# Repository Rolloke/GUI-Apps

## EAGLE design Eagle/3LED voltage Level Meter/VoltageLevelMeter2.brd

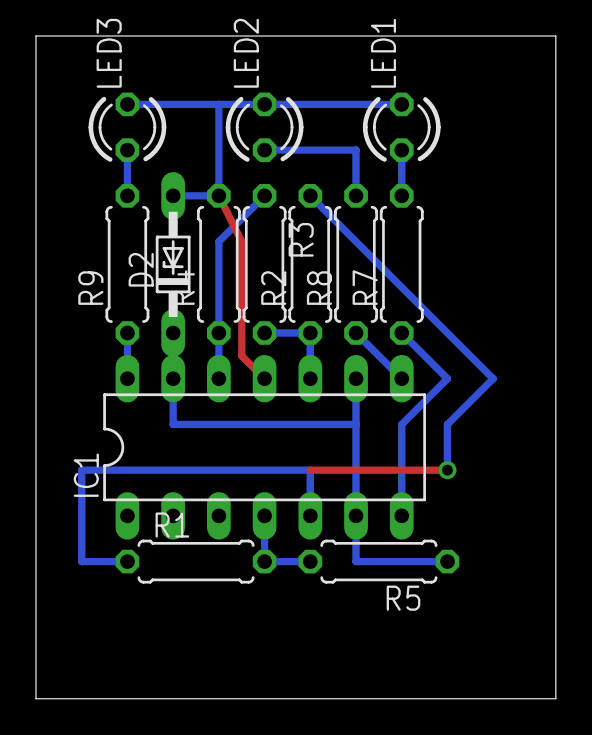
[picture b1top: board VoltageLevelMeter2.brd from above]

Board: 2 copper layers, 28.9 x 36.8 mm, 14 parts (0 on the bottom side), 12 nets.

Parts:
D2: DO34Z7
DRILEGEND: DRILEGEND
IC1: LM324N; DIL14
LED1: red; LED3MM
LED2: Yelllow; LED3MM
LED3: green; LED3MM
R1: 82k; 0207/7
R2: 8k2; 0207/7
R3: 7k5; 0207/7
R4: 33k; 0207/7
R5: 100k; 0207/7
R7, R8, R9: 12k; 0207/7

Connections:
unnamed: IC1.5, R1.1, R2.2
unnamed: IC1.14, R9.1
unnamed: IC1.8, R8.1
unnamed: IC1.7, R7.1
unnamed: IC1.10, R2.1, R3.2
unnamed: IC1.12, R3.1, R4.1
unnamed: LED1.A, R7.2
unnamed: LED2.A, R8.2
unnamed: LED3.A, R9.2
unnamed: D2.C, IC1.6, IC1.9, IC1.13, R5.1
V+: IC1.4, R1.2, R5.2
V-: D2.A, IC1.11, LED1.K, LED2.K, LED3.K, R4.2

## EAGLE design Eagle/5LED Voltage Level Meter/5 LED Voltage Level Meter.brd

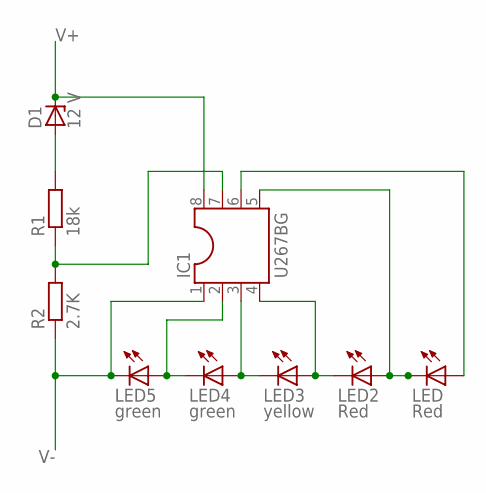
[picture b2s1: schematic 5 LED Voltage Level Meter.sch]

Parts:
D1: 12 V; F126Z10
IC1: U267BG; DIL08
LED, LED2: Red; LED3MM
LED3: yellow; LED3MM
LED4, LED5: green; LED3MM
R1: 18k; 0207/12
R2: 2.7K; 0207/10

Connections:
unnamed: IC1.2, LED4.K (C), LED5.A
unnamed: IC1.3, LED3.K (C), LED4.A
unnamed: IC1.4, LED2.K (C), LED3.A
unnamed: IC1.5, LED.K (C), LED2.A
unnamed: IC1.6, LED.A
unnamed: IC1.7, R1.1, R2.2
unnamed: D1.A, R1.2
V+: D1.C, IC1.8
V-: IC1.1, LED5.K (C), R2.1

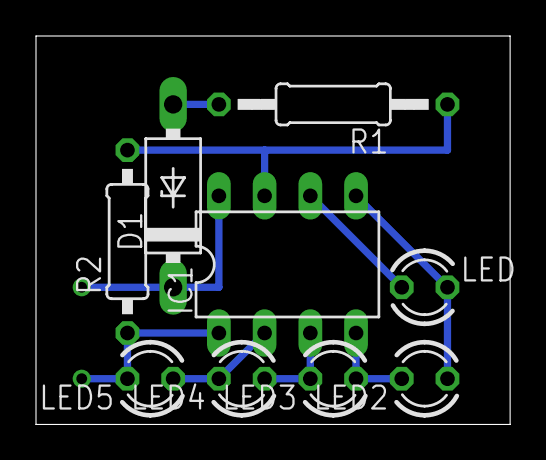
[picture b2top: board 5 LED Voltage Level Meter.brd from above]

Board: 2 copper layers, 26.3 x 21.6 mm, 9 parts (0 on the bottom side), 9 nets.

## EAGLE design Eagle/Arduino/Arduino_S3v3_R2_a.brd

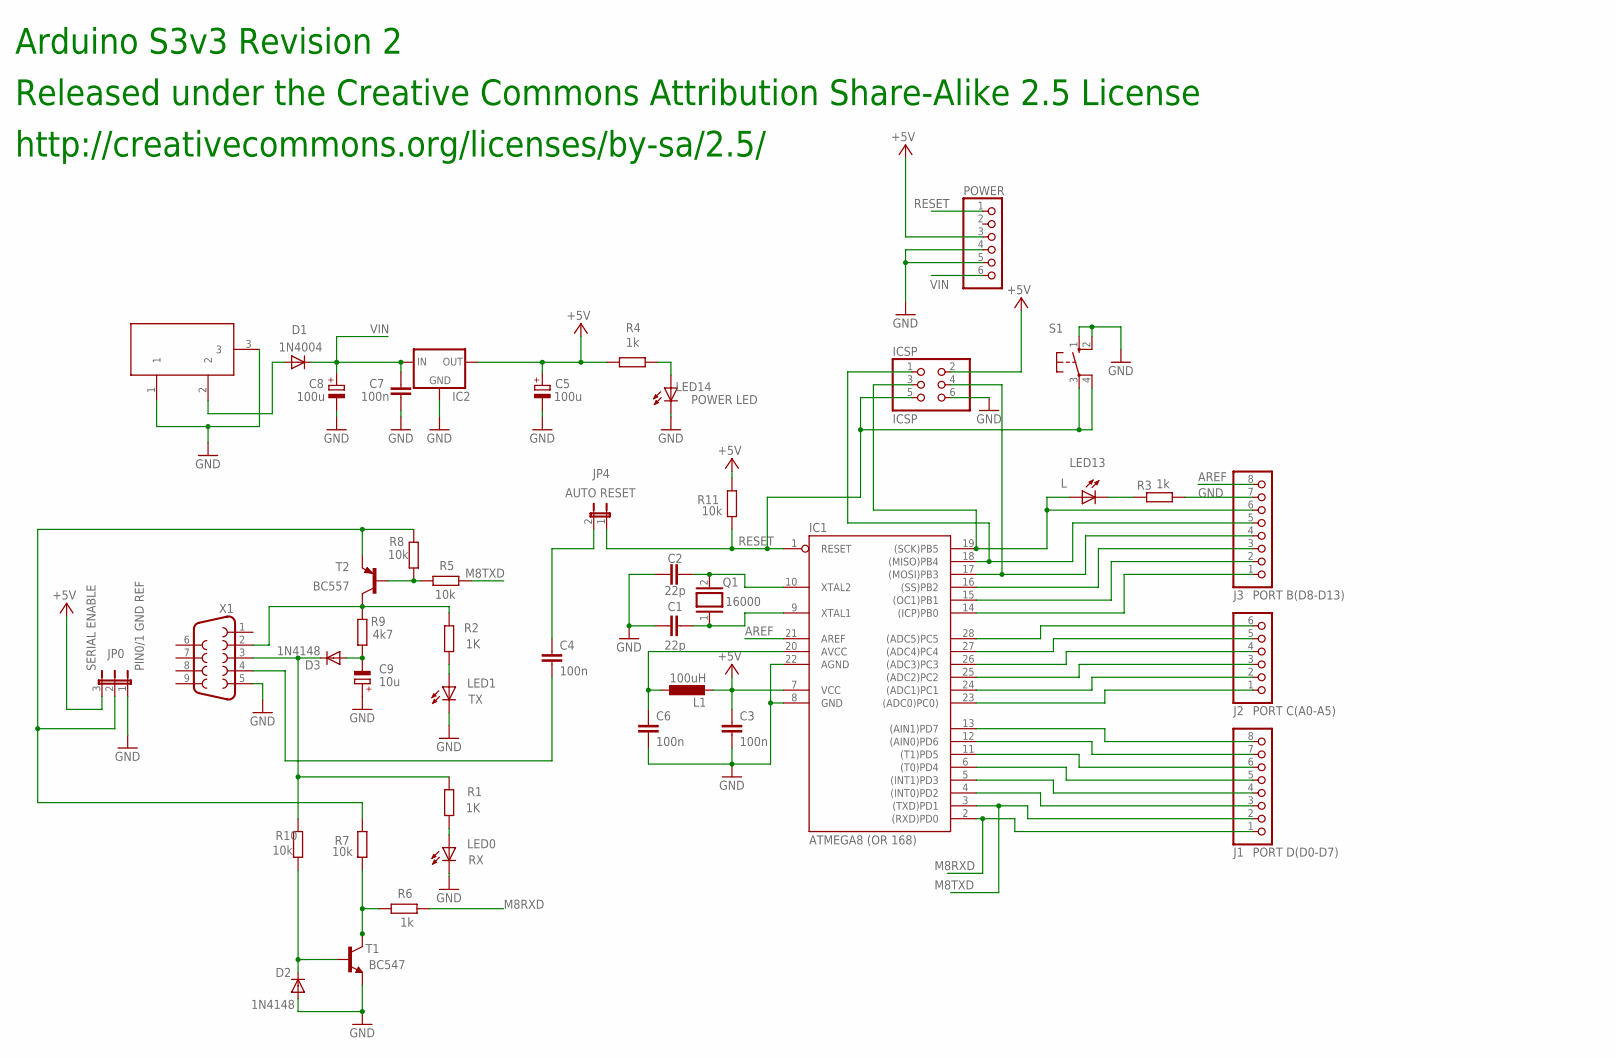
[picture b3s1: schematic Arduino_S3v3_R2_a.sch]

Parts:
C1, C2: 22p; C050-025X075
C3, C4, C6, C7: 100n; C050-025X075
C5, C8: 100u; E3,5-8
C9: 10u; E5-6
D1: 1N4004; DO41-10
D2, D3: 1N4148; DO35-10
DC1: DC21MMX; DC-21MM
IC1: ATMEGA8 (OR 168); DIL28-3
IC2: 78XXL
ICSP: ICSP; 2X03
J1: PORT D(D0-D7); 1X08
J2: PORT C(A0-A5); 1X06
J3: PORT B(D8-D13); 1X08
JP0: JP2W
JP4: AUTO RESET; JP1W
L1: 100uH; 0207/10
LED0: RX; LED3MM
LED1: TX; LED3MM
LED13: L; LED3MM
LED14: POWER LED; LED3MM
POWER: PINHD-1X6; 1X06
Q1: 16000; Q
R1, R2: 1K; 0207/10
R3, R4, R6: 1k; 0207/10
R5, R7, R8, R10, R11: 10k; 0207/10
R9: 4k7; 0207/10
S1: 10-XX; B3F-10XX
T1: BC547; TO92
T2: BC557; TO92-EBC
X1: F09H

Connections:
+5V: C3.1, C5.+, IC1.7 (VCC), IC2.OUT, ICSP.2, JP0.3, L1.2, POWER.3, R4.2, R11.2
AREF: IC1.21 (AREF), J3.8
GND: C1.1, C2.1, C3.2, C5.-, C6.2, C7.1, C8.-, C9.+, D2.A, DC1.1, DC1.3, IC1.8 (GND), IC1.22 (AGND), IC2.GND, ICSP.6, J3.7, JP0.1, LED0.K (C), LED1.K (C), LED14.K (C), POWER.4, POWER.5, R3.1, S1.1 (S), S1.2 (S1), T1.1 (E), X1.5
M8RXD: IC1.2 ((RXD)PD0), J1.1, R6.1
M8TXD: IC1.3 ((TXD)PD1), J1.2, R5.1
unnamed: IC1.18 ((MISO)PB4), ICSP.1, J3.5
unnamed: C9.-, D3.A, R9.1
unnamed: LED14.A, R4.1
unnamed: IC1.17 ((MOSI)PB3), ICSP.4, J3.4
unnamed: IC1.14 ((ICP)PB0), J3.1
unnamed: C1.2, IC1.9 (XTAL1), Q1.1
unnamed: C2.2, IC1.10 (XTAL2), Q1.2
unnamed: D1.A, DC1.2
unnamed: IC1.4 ((INT0)PD2), J1.3
unnamed: IC1.5 ((INT1)PD3), J1.4
unnamed: IC1.6 ((T0)PD4), J1.5
unnamed: IC1.11 ((T1)PD5), J1.6
unnamed: IC1.12 ((AIN0)PD6), J1.7
unnamed: IC1.13 ((AIN1)PD7), J1.8
unnamed: IC1.23 ((ADC0)PC0)), J2.1
unnamed: IC1.24 ((ADC1)PC1), J2.2
unnamed: IC1.25 ((ADC2)PC2), J2.3
unnamed: IC1.26 ((ADC3)PC3), J2.4
unnamed: IC1.27 ((ADC4)PC4), J2.5
unnamed: IC1.28 ((ADC5)PC5), J2.6
unnamed: IC1.15 ((OC1)PB1), J3.2
unnamed: IC1.16 ((SS)PB2), J3.3
unnamed: D3.C, R1.2, R10.2, X1.3
unnamed: R6.2, R7.1, T1.3 (C)
unnamed: R5.2, R8.2, T2.B
unnamed: D2.C, R10.1, T1.2 (B)
unnamed: LED13.K (C), R3.2
unnamed: LED1.A, R2.1
unnamed: LED0.A, R1.1
unnamed: C4.1, JP4.2
unnamed: C4.2, X1.4
unnamed: R2.2, R9.2, T2.C, X1.2
unnamed: C6.1, IC1.20 (AVCC), L1.1
RESET: IC1.1 (RESET), ICSP.5, JP4.1, POWER.1, R11.1, S1.3, S1.4 (P1)
SCK: IC1.19 ((SCK)PB5), ICSP.3, J3.6, LED13.A
SERIAL_VCC: JP0.2, R7.2, R8.1, T2.E
VIN: C7.2, C8.+, D1.C, IC2.IN, POWER.6

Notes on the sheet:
PIN0/1 GND REF
SERIAL ENABLE
Released under the Creative Commons Attribution Share-Alike 2.5 License
http://creativecommons.org/licenses/by-sa/2.5/
Arduino S3v3 Revision 2

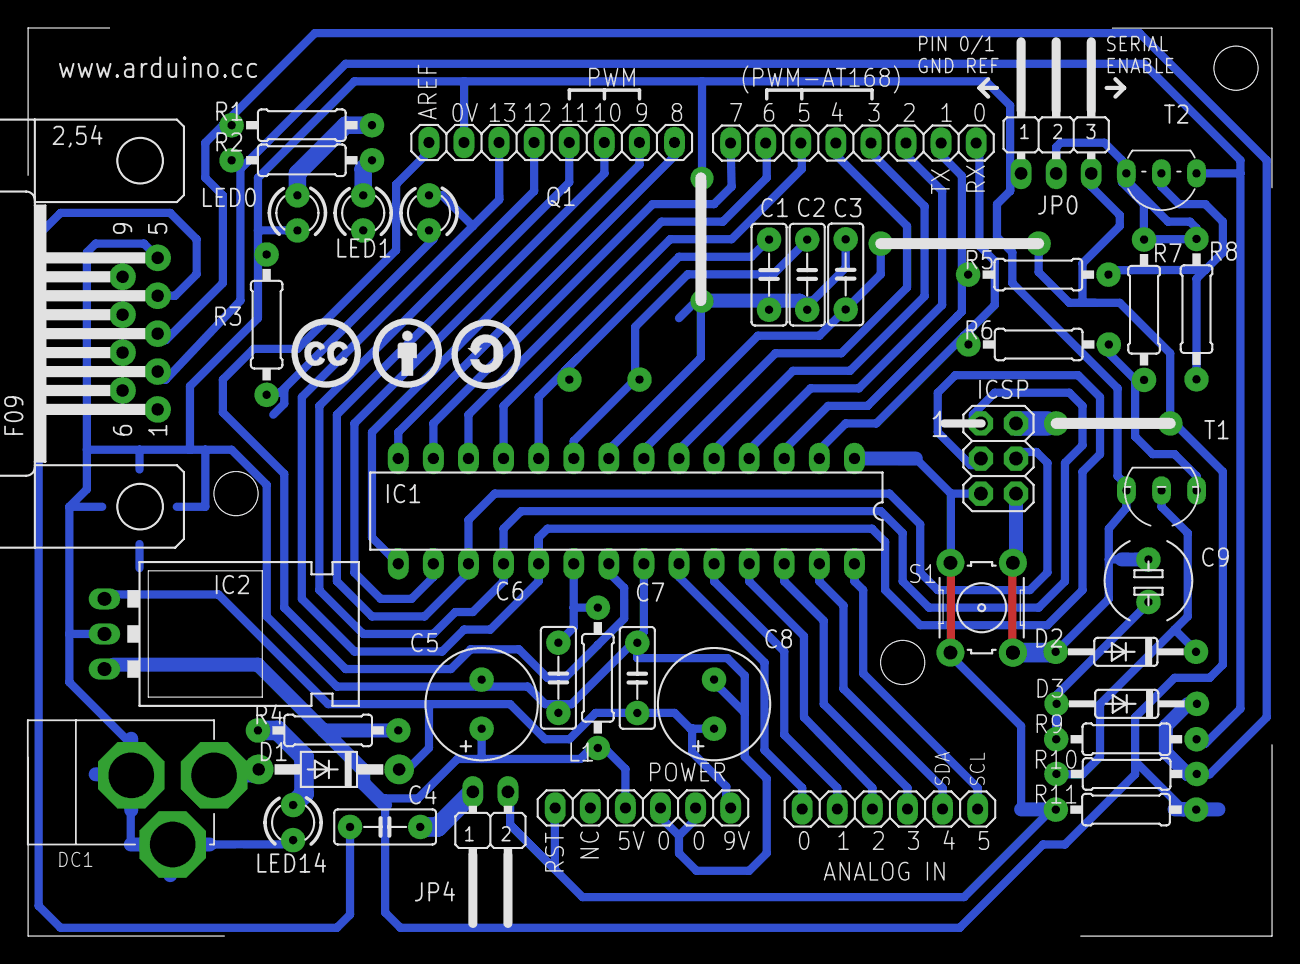
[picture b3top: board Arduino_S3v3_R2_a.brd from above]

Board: 2 copper layers, 90.1 x 65.7 mm, 46 parts (1 on the bottom side), 42 nets.

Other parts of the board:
U$1: CC
U$2: BY
U$3: SA

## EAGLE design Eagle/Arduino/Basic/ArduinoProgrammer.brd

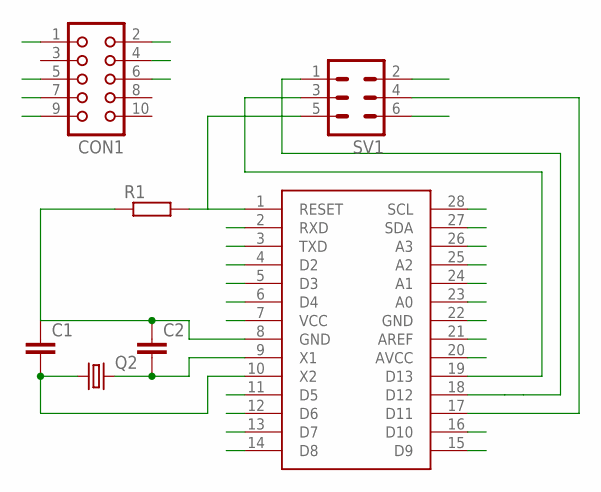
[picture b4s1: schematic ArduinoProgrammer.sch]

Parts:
C1, C2: C-EU025-024X044; C025-024X044
CON1: CON10
Q2: CRYSTALHC49S; HC49/S
R1: R-EU_0207/10; 0207/10
SV1: MA03-2
U$1: ATMEGA328P-PU; DIL28-3

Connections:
A0[MODE]: U$1.23 (A0)
A1: U$1.24 (A1)
A2[MIN]: U$1.25 (A2)
A3[AL]: U$1.26 (A3)
A4[SDA]: U$1.27 (SDA)
A5[SCL]: U$1.28 (SCL)
AREF: U$1.21 (AREF)
DIO1(TX): U$1.3 (TXD)
DIO2[L0]: U$1.4 (D2)
DIO3(PWM)[TONE]: U$1.5 (D3)
DIO4[L1]: U$1.6 (D4)
DIO5(PWM)[AM]: U$1.11 (D5)
DIO6(PWM)[AH]: U$1.12 (D6)
DIO7[L2]: U$1.13 (D7)
DIO8[L3]: U$1.14 (D8)
DIO9(PWM)[SEC]: U$1.15 (D9)
DIO10(PWM)[MIN]: U$1.16 (D10)
DIO11(PWM)MOSI[HR]: CON1.1, SV1.4, U$1.17 (D11)
DIO12/MISO[L4]: CON1.9, SV1.1, U$1.18 (D12)
DPIO0(RX): U$1.2 (RXD)
GND: C1.1, C2.1, CON1.4, R1.1, SV1.6, U$1.8 (GND), U$1.22 (GND)
RESET: R1.2, SV1.5, U$1.1 (RESET)
SCK[L5]: CON1.7, SV1.3, U$1.19 (D13)
VCC: CON1.2, SV1.2, U$1.7 (VCC), U$1.20 (AVCC)
X1: C2.2, Q2.2, U$1.9 (X1)
X2: C1.2, Q2.1, U$1.10 (X2)

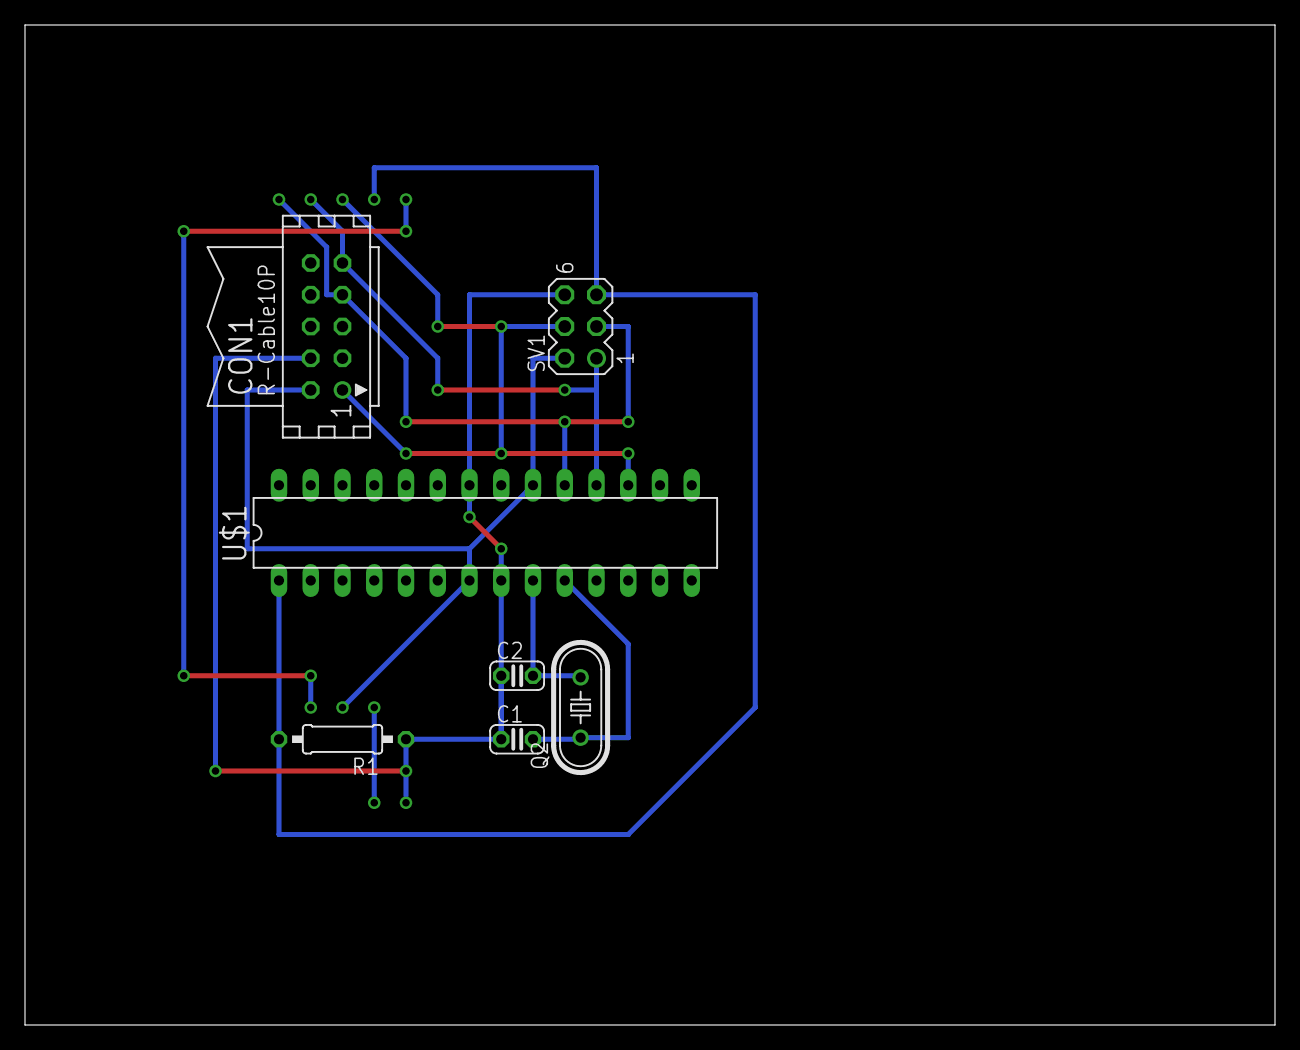
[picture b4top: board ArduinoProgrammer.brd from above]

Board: 2 copper layers, 100.0 x 80.0 mm, 7 parts (0 on the bottom side), 8 nets.

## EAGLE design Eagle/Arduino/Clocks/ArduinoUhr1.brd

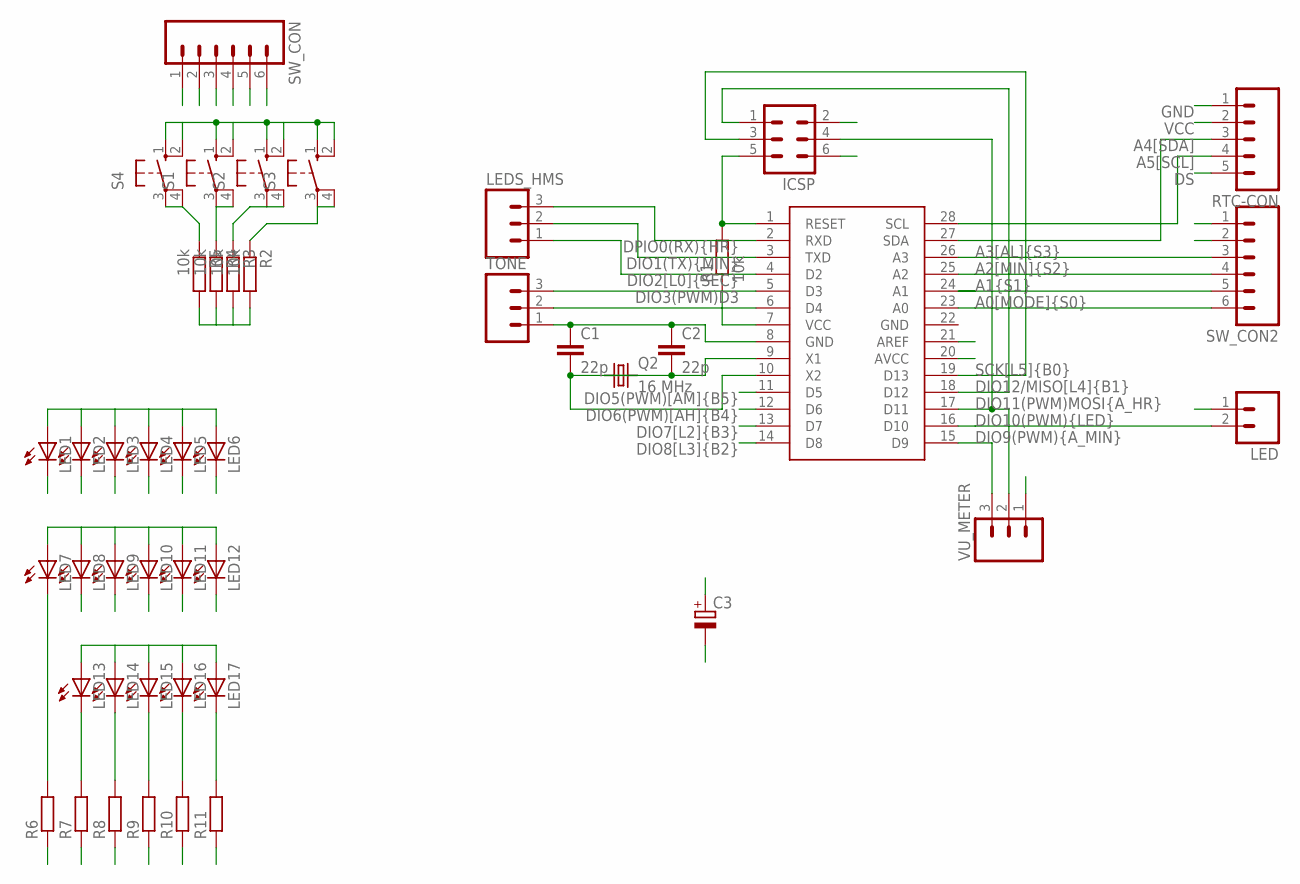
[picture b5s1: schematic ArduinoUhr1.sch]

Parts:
C1, C2: 22p; C025-024X044
C3: CPOL-EUE5-10.5; E5-10,5
ICSP: MA03-2
LED: M02; 02P
LED1, LED2, LED3, LED4, LED5, LED6, LED7, LED8, LED9, LED10, LED11, LED12: LED3MM
LED13, LED14, LED15, LED16, LED17: LED5MM
LEDS_HMS: M03; 03P
Q2: 16 MHz; HC49/S
R1: 10k; 0207/15
R2, R3, R4, R5: 10k; 0204/5
R6, R7, R8, R9, R10, R11: R-EU_0204/7; 0204/7
RTC-CON: M05; 05P
S1, S2, S3, S4: 40-XX; B3F-40XX
SW_CON, SW_CON2: M06; 06P
TONE: M03; 03P
U$1: ATMEGA328P-PU; DIL28-3
VU_METER: M03; 03P

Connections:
A0[MODE]{S0}: SW_CON2.6, U$1.23 (A0)
A1{S1}: SW_CON2.5, U$1.24 (A1)
A2[MIN]{S2}: SW_CON2.4, U$1.25 (A2)
A3[AL]{S3}: SW_CON2.3, U$1.26 (A3)
A4[SDA]: RTC-CON.3, U$1.27 (SDA)
A5[SCL]: RTC-CON.4, U$1.28 (SCL)
AREF: U$1.21 (AREF)
BIT0: R11.1
BIT1: R10.1
BIT2: R9.1
BIT3: R8.1
BIT4: R7.1
BIT5: R6.1
D4: TONE.2, U$1.6 (D4)
DIO1(TX){MIN}: LED7.A, LED8.A, LED9.A, LED10.A, LED11.A, LED12.A, LEDS_HMS.2, U$1.3 (TXD)
DIO2[L0]{SEC}: LED1.A, LED2.A, LED3.A, LED4.A, LED5.A, LED6.A, LEDS_HMS.1, U$1.4 (D2)
DIO3(PWM)D3: TONE.3, U$1.5 (D3)
DIO5(PWM)[AM]{B5}: U$1.11 (D5)
DIO6(PWM)[AH]{B4}: U$1.12 (D6)
DIO7[L2]{B3}: U$1.13 (D7)
DIO8[L3]{B2}: U$1.14 (D8)
DIO9(PWM){A_MIN}: U$1.15 (D9), VU_METER.3
DIO10(PWM){LED}: LED.2, U$1.16 (D10)
DIO11(PWM)MOSI{A_HR}: ICSP.4, U$1.17 (D11), VU_METER.2
DIO12/MISO[L4]{B1}: ICSP.1, U$1.18 (D12)
DPIO0(RX){HR}: LED13.A, LED14.A, LED15.A, LED16.A, LED17.A, LEDS_HMS.3, U$1.2 (RXD)
DS: RTC-CON.5
GND: C1.1, C2.1, C3.-, ICSP.6, LED.1, RTC-CON.1, SW_CON2.2, TONE.1, U$1.8 (GND), VU_METER.1
GND_SW: R2.2, R3.2, R4.2, R5.2, SW_CON.2
LED0: LED6.K (C), LED12.K (C), LED17.K (C), R11.2
LED1: LED5.K (C), LED11.K (C), LED16.K (C), R10.2
LED2: LED4.K (C), LED10.K (C), LED15.K (C), R9.2
LED3: LED3.K (C), LED9.K (C), LED14.K (C), R8.2
LED4: LED2.K (C), LED8.K (C), LED13.K (C), R7.2
LED5: LED1.K (C), LED7.K (C), R6.2
RESET: ICSP.5, R1.2, U$1.1 (RESET)
SCK[L5]{B0}: ICSP.3, U$1.19 (D13)
SW1: R5.1, S4.3, S4.4 (P1), SW_CON.3
SW2: R4.1, S1.3, S1.4 (P1), SW_CON.4
SW3: R3.1, S2.3, S2.4 (P1), SW_CON.5
SW4: R2.1, S3.3, S3.4 (P1), SW_CON.6
VCC: C3.+, ICSP.2, R1.1, RTC-CON.2, SW_CON2.1, U$1.7 (VCC), U$1.20 (AVCC)
VCC_SW: S1.1 (S), S1.2 (S1), S2.1 (S), S2.2 (S1), S3.1 (S), S3.2 (S1), S4.1 (S), S4.2 (S1), SW_CON.1
X1: C2.2, Q2.1, U$1.9 (X1)
X2: C1.2, Q2.2, U$1.10 (X2)

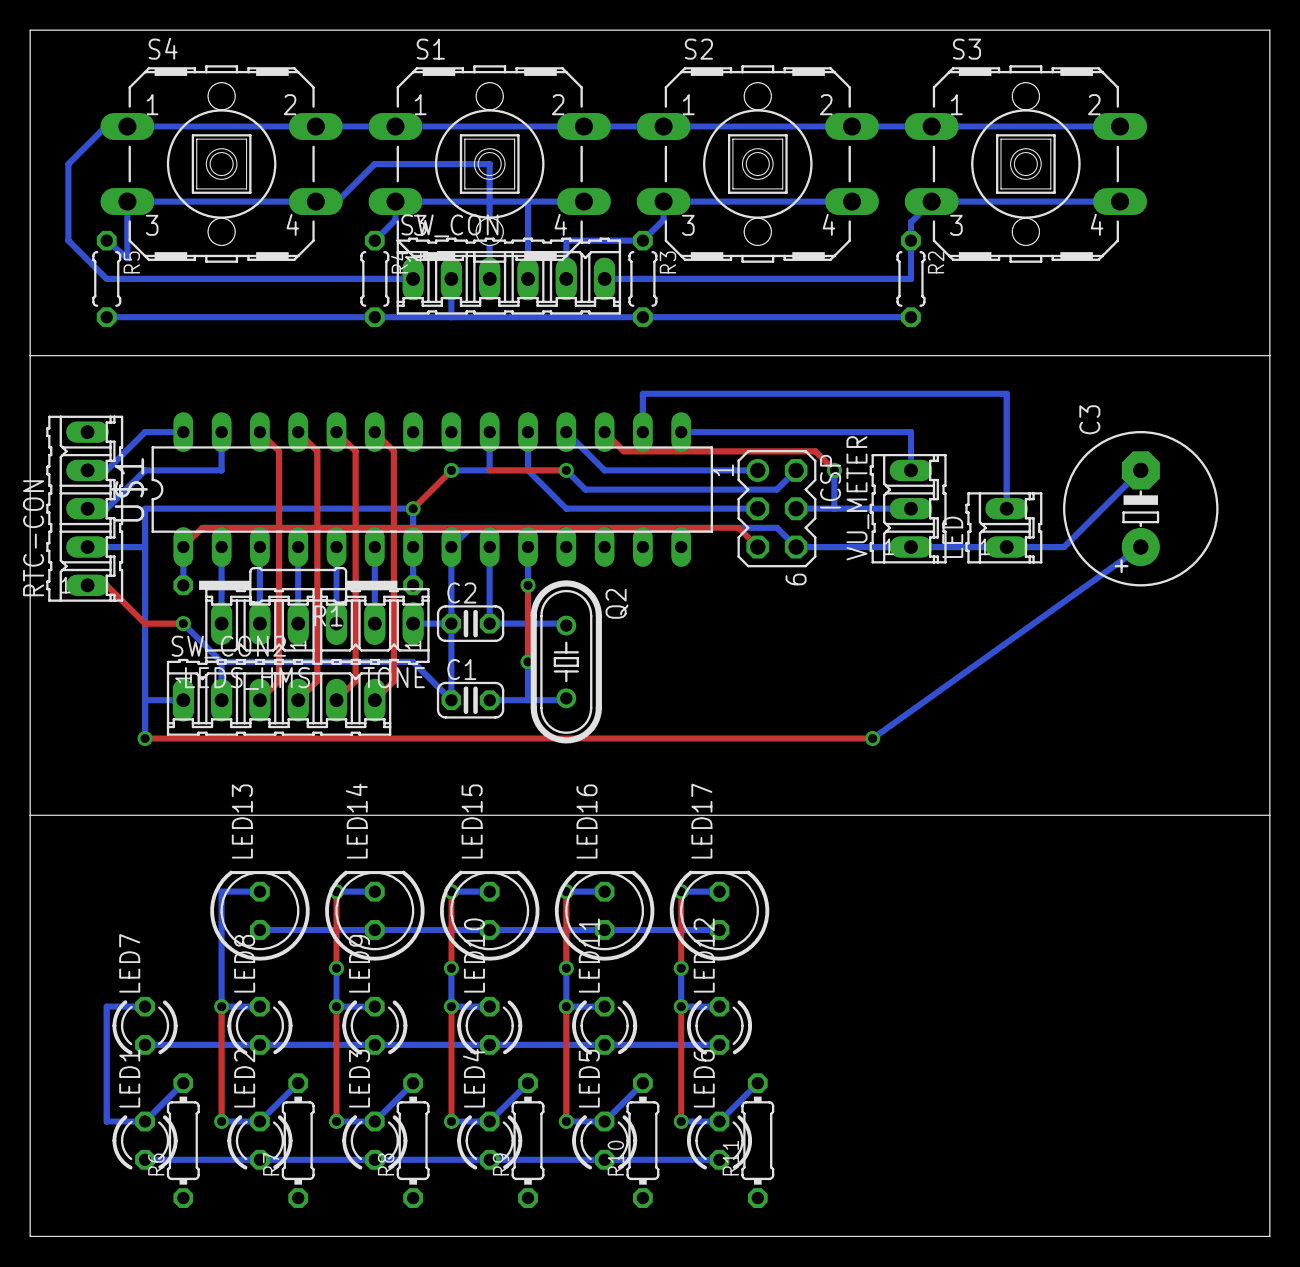
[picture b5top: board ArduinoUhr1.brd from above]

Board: 2 copper layers, 82.2 x 80.0 mm, 45 parts (0 on the bottom side), 33 nets.

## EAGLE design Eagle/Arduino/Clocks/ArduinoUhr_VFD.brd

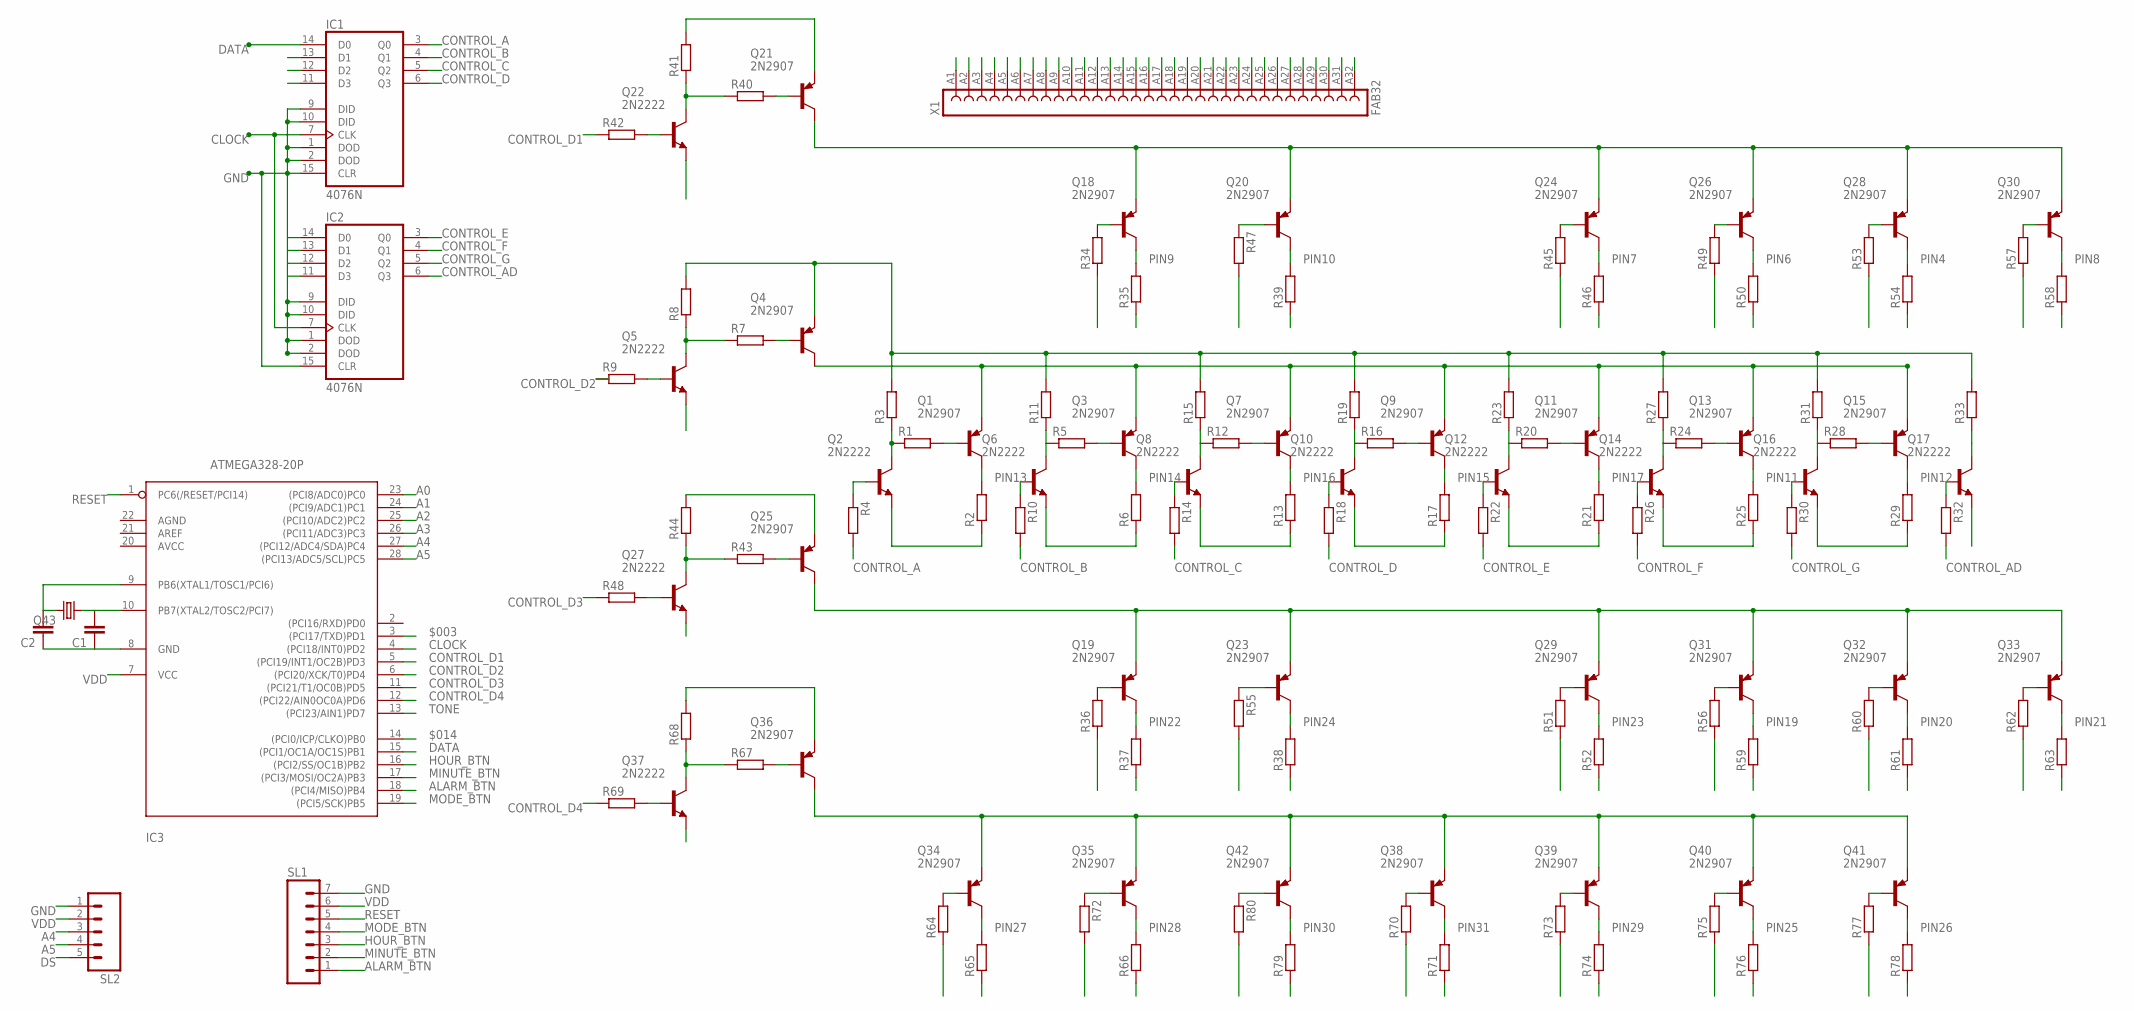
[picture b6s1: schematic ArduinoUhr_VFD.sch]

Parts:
C1, C2: C-EU025-024X044; C025-024X044
IC1, IC2: 4076N; DIL16
IC3: ATMEGA328-20P; DIL28-3
Q1, Q3, Q4, Q7, Q9, Q11, Q13, Q15, Q18, Q19, Q20, Q21, Q23, Q24, Q25, Q26, Q28, Q29, Q30, Q31, Q32, Q33, Q34, Q35, Q36, Q38, Q39, Q40, Q41, Q42: 2N2907; TO18
Q2, Q5, Q6, Q8, Q10, Q12, Q14, Q16, Q17, Q22, Q27, Q37: 2N2222; TO18
Q43: CRYSTALHC49S; HC49/S
R1, R12, R20, R28, R34, R53, R55, R57, R60, R62, R72, R73, R75: R-EU_0411/3V; 0411V
R2, R3, R4, R5, R6, R9, R10, R11, R13, R14, R15, R16, R17, R18, R19, R21, R22, R23, R24, R25, R26, R27, R29, R30, R31, R32, R33, R35, R36, R37, R38, R39, R42, R45, R46, R47, R48, R49, R50, R51, R52, R54, R56, R58, R59, R61, R63, R64, R65, R66, R69, R70, R71, R74, R76, R77, R78, R79, R80: R-EU_0204/7; 0204/7
R7, R8, R40, R41, R43, R44, R67, R68: R-EU_0204/2V; 0204V
SL1: M07; 07P
SL2: M05; 05P
X1: FAB32

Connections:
$003: IC3.3 ((PCI17/TXD)PD1)
$014: IC3.14 ((PCI0/ICP/CLKO)PB0)
A0: IC3.23 ((PCI8/ADC0)PC0)
A1: IC3.24 ((PCI9/ADC1)PC1)
A2: IC3.25 ((PCI10/ADC2)PC2)
A3: IC3.26 ((PCI11/ADC3)PC3)
A4: IC3.27 ((PCI12/ADC4/SDA)PC4), SL2.3
A5: IC3.28 ((PCI13/ADC5/SCL)PC5), SL2.4
ALARM_BTN: IC3.18 ((PCI4/MISO)PB4), SL1.1
CI_A: Q2.3 (C), R1.1, R3.1, R64.1
CI_AD: Q17.3 (C), R33.1, R57.1, R62.1
CI_B: Q6.3 (C), R5.1, R11.1, R34.1, R36.1, R72.2
CI_C: Q8.3 (C), R12.1, R15.1, R47.2, R55.2, R80.2
CI_D: Q10.3 (C), R16.1, R19.1, R70.1
CI_E: Q12.3 (C), R20.1, R23.1, R45.1, R51.1, R73.1
CI_F: Q14.3 (C), R24.1, R27.1, R49.1, R56.1, R75.1
CI_G: Q16.3 (C), R28.1, R31.1, R53.1, R60.1, R77.1
CLOCK: IC1.7 (CLK), IC2.7 (CLK), IC3.4 ((PCI18/INT0)PD2)
CONTROL_A: IC1.3 (Q0), IC1.13 (D1), R4.2
CONTROL_AD: IC2.6 (Q3), R32.2
CONTROL_B: IC1.4 (Q1), IC1.12 (D2), R10.2
CONTROL_C: IC1.5 (Q2), IC1.11 (D3), R14.2
CONTROL_D: IC1.6 (Q3), IC2.14 (D0), R18.2
CONTROL_D1: IC3.5 ((PCI19/INT1/OC2B)PD3), R42.1
CONTROL_D2: IC3.6 ((PCI20/XCK/T0)PD4), R9.1
CONTROL_D3: IC3.11 ((PCI21/T1/OC0B)PD5), R48.1
CONTROL_D4: IC3.12 ((PCI22/AIN0OC0A)PD6), R69.1
CONTROL_E: IC2.3 (Q0), IC2.13 (D1), R22.2
CONTROL_F: IC2.4 (Q1), IC2.12 (D2), R26.2
CONTROL_G: IC2.5 (Q2), IC2.11 (D3), R30.2
DATA: IC1.14 (D0), IC3.15 ((PCI1/OC1A/OC1S)PB1)
DS: SL2.5
GND: C1.1, C2.1, IC1.1 (DOD), IC1.2 (DOD), IC1.9 (DID), IC1.10 (DID), IC1.15 (CLR), IC2.1 (DOD), IC2.2 (DOD), IC2.9 (DID), IC2.10 (DID), IC2.15 (CLR), IC3.8 (GND), Q2.1 (E), Q5.1 (E), Q6.1 (E), Q8.1 (E), Q10.1 (E), Q12.1 (E), Q14.1 (E), Q16.1 (E), Q17.1 (E), Q22.1 (E), Q27.1 (E), Q37.1 (E), R2.1, R6.1, R13.1, R17.1, R21.1, R25.1, R29.1, R35.1, R37.1, R38.1, R39.1, R46.1, R50.1, R52.1, R54.1, R58.1, R59.1, R61.1, R63.1, R65.1, R66.1, R71.1, R74.1, R76.1, R78.1, R79.1, SL1.7, SL2.1
HOUR_BTN: IC3.16 ((PCI2/SS/OC1B)PB2), SL1.3
MINUTE_BTN: IC3.17 ((PCI3/MOSI/OC2A)PB3), SL1.2
MODE_BTN: IC3.19 ((PCI5/SCK)PB5), SL1.4
unnamed: Q5.2 (B), R9.2
unnamed: Q35.2 (B), R72.1
unnamed: Q1.2 (B), R1.2
unnamed: Q42.2 (B), R80.1
unnamed: Q3.2 (B), R5.2
unnamed: Q2.2 (B), R4.1
unnamed: Q4.2 (B), R7.2
unnamed: Q5.3 (C), R7.1, R8.1
unnamed: Q18.2 (B), R34.2
unnamed: Q6.2 (B), R10.1
unnamed: Q23.2 (B), R55.1
unnamed: Q20.2 (B), R47.1
unnamed: Q15.2 (B), R28.2
unnamed: Q7.2 (B), R12.2
unnamed: Q21.2 (B), R40.2
unnamed: Q8.2 (B), R14.1
unnamed: Q17.2 (B), R32.1
unnamed: C1.2, IC3.10 (PB7(XTAL2/TOSC2/PCI7)), Q43.1
unnamed: Q22.3 (C), R40.1, R41.1
unnamed: Q9.2 (B), R16.2
unnamed: Q22.2 (B), R42.2
unnamed: Q10.2 (B), R18.1
unnamed: C2.2, IC3.9 (PB6(XTAL1/TOSC1/PCI6)), Q43.2
unnamed: Q16.2 (B), R30.1
unnamed: Q11.2 (B), R20.2
unnamed: Q12.2 (B), R22.1
unnamed: Q24.2 (B), R45.2
unnamed: Q13.2 (B), R24.2
unnamed: Q14.2 (B), R26.1
unnamed: Q26.2 (B), R49.2
unnamed: Q19.2 (B), R36.2
unnamed: Q28.2 (B), R53.2
unnamed: Q25.2 (B), R43.2
unnamed: Q30.2 (B), R57.2
unnamed: Q27.3 (C), R43.1, R44.1
unnamed: Q27.2 (B), R48.2
unnamed: Q29.2 (B), R51.2
unnamed: Q31.2 (B), R56.2
unnamed: Q32.2 (B), R60.2
unnamed: Q33.2 (B), R62.2
unnamed: Q34.2 (B), R64.2
unnamed: Q36.2 (B), R67.2
unnamed: Q37.3 (C), R67.1, R68.1
unnamed: Q37.2 (B), R69.2
unnamed: Q38.2 (B), R70.2
unnamed: Q39.2 (B), R73.2
unnamed: Q40.2 (B), R75.2
unnamed: Q41.2 (B), R77.2
PIN1: X1.A1 (1)
PIN2: X1.A2 (2)
PIN3: X1.A3 (3)
PIN4: Q28.3 (C), R54.2, X1.A4 (4)
PIN5: X1.A5 (5)
PIN6: Q26.3 (C), R50.2, X1.A6 (6)
PIN7: Q24.3 (C), R46.2, X1.A7 (7)
PIN8: Q30.3 (C), R58.2, X1.A8 (8)
PIN9: Q18.3 (C), R35.2, X1.A9 (9)
PIN10: Q20.3 (C), R39.2, X1.A10 (10)
PIN11: Q13.3 (C), R25.2, X1.A11 (11)
PIN12: Q15.3 (C), R29.2, X1.A12 (12)
PIN13: Q1.3 (C), R2.2, X1.A13 (13)
PIN14: Q3.3 (C), R6.2, X1.A14 (14)
PIN15: Q9.3 (C), R17.2, X1.A15 (15)
PIN16: Q7.3 (C), R13.2, X1.A16 (16)
PIN17: Q11.3 (C), R21.2, X1.A17 (17)
PIN18: X1.A18 (18)
PIN19: Q31.3 (C), R59.2, X1.A19 (19)
PIN20: Q32.3 (C), R61.2, X1.A20 (20)
PIN21: Q33.3 (C), R63.2, X1.A21 (21)
PIN22: Q19.3 (C), R37.2, X1.A22 (22)
PIN23: Q29.3 (C), R52.2, X1.A23 (23)
PIN24: Q23.3 (C), R38.2, X1.A24 (24)
PIN25: Q40.3 (C), R76.2, X1.A25 (25)
PIN26: Q41.3 (C), R78.2, X1.A26 (26)
PIN27: Q34.3 (C), R65.2, X1.A27 (27)
PIN28: Q35.3 (C), R66.2, X1.A28 (28)
PIN29: Q39.3 (C), R74.2, X1.A29 (29)
PIN30: Q42.3 (C), R79.2, X1.A30 (30)
PIN31: Q38.3 (C), R71.2, X1.A31 (31)
PIN32: X1.A32 (32)
RESET: IC3.1 (PC6(/RESET/PCI14)), SL1.5
TONE: IC3.13 ((PCI23/AIN1)PD7)
VDD: IC1.16 (VDD), IC2.16 (VDD), IC3.7 (VCC), SL1.6, SL2.2
VSS: IC1.8 (VSS), IC2.8 (VSS)
V_D1: Q18.1 (E), Q20.1 (E), Q21.3 (C), Q24.1 (E), Q26.1 (E), Q28.1 (E), Q30.1 (E)
V_D2: Q1.1 (E), Q3.1 (E), Q4.3 (C), Q7.1 (E), Q9.1 (E), Q11.1 (E), Q13.1 (E), Q15.1 (E)
V_D3: Q19.1 (E), Q23.1 (E), Q25.3 (C), Q29.1 (E), Q31.1 (E), Q32.1 (E), Q33.1 (E)
V_D4: Q34.1 (E), Q35.1 (E), Q36.3 (C), Q38.1 (E), Q39.1 (E), Q40.1 (E), Q41.1 (E), Q42.1 (E)
V_VFD: Q4.1 (E), Q21.1 (E), Q25.1 (E), Q36.1 (E), R3.2, R8.2, R11.2, R15.2, R19.2, R23.2, R27.2, R31.2, R33.2, R41.2, R44.2, R68.2

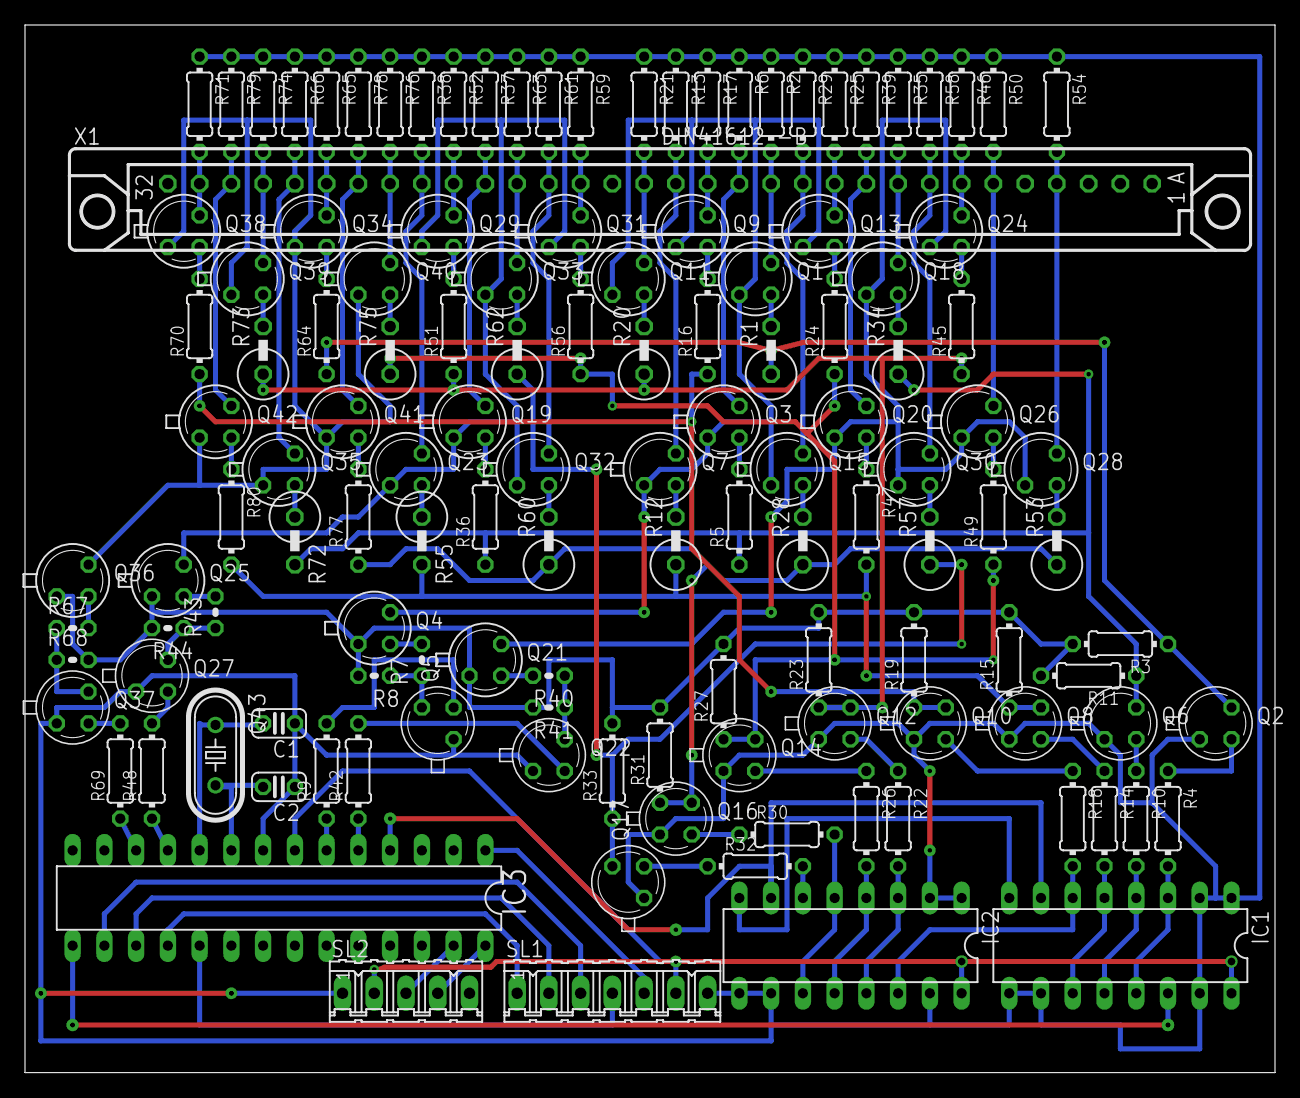
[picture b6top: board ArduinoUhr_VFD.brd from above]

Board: 2 copper layers, 100.0 x 83.8 mm, 131 parts (0 on the bottom side), 111 nets.

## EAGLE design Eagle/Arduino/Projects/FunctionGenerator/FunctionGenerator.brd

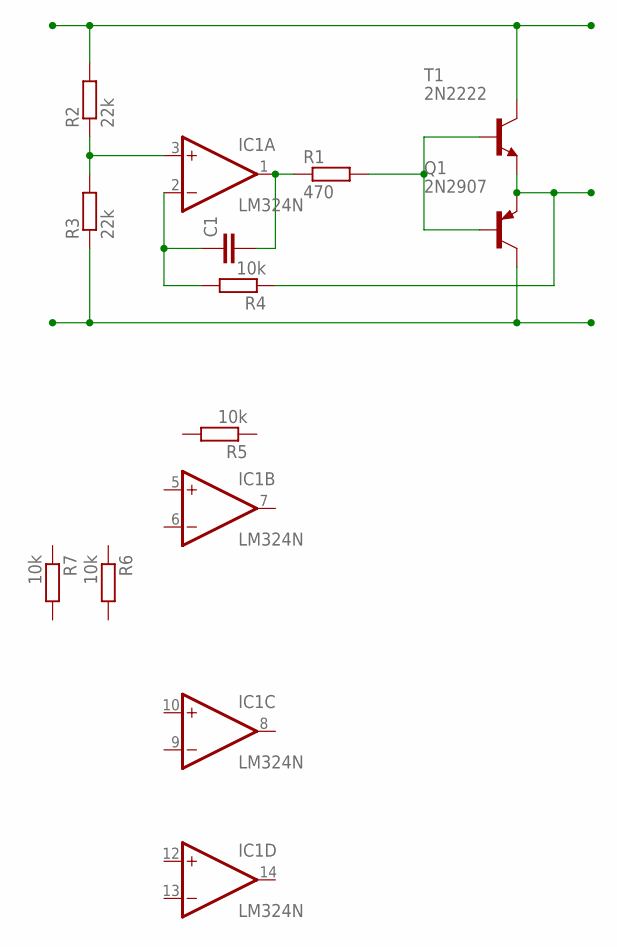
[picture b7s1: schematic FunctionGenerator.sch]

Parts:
C1: C-EU050-025X075; C050-025X075
IC1: LM324N; DIL14
Q1: 2N2907; TO18
R1: 470; 0207/10
R2, R3: 22k; 0207/10
R4, R5, R6, R7: 10k; 0207/10
T1: 2N2222; TO18

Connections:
unnamed: Q1.2 (B), R1.2, T1.2 (B)
unnamed: C1.2, IC1.1 (OUT), R1.1
unnamed: IC1.3 (+IN), R2.1, R3.2
unnamed: Q1.1 (E), R4.1, T1.1 (E)
unnamed: C1.1, IC1.2 (-IN), R4.2
V+: IC1.4 (V+), R2.2, T1.3 (C)
V-: IC1.11 (V-), Q1.3 (C), R3.1

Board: 2 copper layers, 11 parts (0 on the bottom side), 7 nets, no tracks yet.

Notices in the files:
Eagle/Arduino/Arduino_S3v3_R2_a.brd:
CC BY SA 2.5
